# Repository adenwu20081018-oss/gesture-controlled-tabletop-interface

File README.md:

# Gesture-Controlled Tabletop Interface

A camera-based interface for controlling applications with hand gestures. Guess Who is the first application I used to demonstrate it.

[Setup](docs/setup.md) · [Hardware files](hardware/README.md) · [Tests](docs/testing.md)

## Why I Built This

Back in high school, during my Grade 11 year, I spent a lot of time working on this ISP Guess Who game. This game was one of the starting points that sparked my interest in programming and building a game of my own from scratch, from designing the characters and GUI to creating the music. After finishing it, I wasn't satisfied with just letting all that hard work sit in a folder on my computer. I wanted to find a way to bring the game back and do something different with it. With the naive idea of recreating Iron Man's JARVIS system, I decided to try implementing my game in a completely different way, turning it into an interactive tabletop game and controlling it with hand gestures directly on the table.

## How It Works

Camera → Python/OpenCV/MediaPipe → Java Guess Who → Arduino Mega 2560

Python tracks my fingertip and detects a pinch as a selection. Four-point camera calibration maps the interaction area into the game window. Python sends the selection over TCP, and Java uses the same button actions as a mouse click. The Mega's onboard LED responds to character-card actions through USB serial.

I have tested mouse and webcam-pinch control with Arduino LED feedback on my laptop. The resizable interface is ready for a future projector setup, but I have not physically tested tabletop projection or an external webcam yet.

## Hardware

My main prototype uses an ELEGOO Mega 2560, a 400-point half-size breadboard, jumper wires and a PN2222/2N2222A transistor-driven 5V active buzzer. The circuit includes a 470Ω base resistor, 10kΩ pull-down and 1N4007 diode. I have tested the wiring and confirmed that the buzzer works. BUZZ is a standalone command; automatic game sound is not integrated.

[Editable drawing and connections](hardware/breadboard/README.md). My laptop and built-in webcam handle input; a projector is the intended tabletop display. The D13 LED is already on the Mega, so there is no external LED circuit.

## Build Photos

I'll add my own hardware photographs here. Images belong in [photos/](photos/README.md).

<!-- Add real photos here, for example:  -->

## Setup and Files

Start with the [Windows setup guide](docs/setup.md) to install the dependencies, build Java and run hand tracking. Run commands from the repository root so the game can find its assets. See [testing](docs/testing.md) for repeatable checks and [projector setup](docs/projector-setup.md) for calibration and future display use.

| Folder | Contents |
| --- | --- |
| `src/` | Java game and input integration |
| `computer-vision/` | Python hand tracking, pinch detection and calibration |
| `assets/` | Button images, character portraits, interface artwork and audio |
| `arduino/` | Mega firmware, Java serial controller and hardware-free tests |
| `hardware/` | Breadboard drawing and concept PCB design |
| `photos/`, `screenshots/` | Future real build photos and actual game captures |
| `docs/`, `tests/` | Supporting guides and regression tests |

## Challenges Faced

## **Next Step: Concept PCB Design**

I designed this PCB in KiCad to bring the working breadboard buzzer circuit onto a dedicated board. The [editable schematic and routed PCB files](hardware/kicad/buzzer-driver-pcb/) include the components, footprints and copper traces. Fabricating and testing the assembled PCB is the next step.

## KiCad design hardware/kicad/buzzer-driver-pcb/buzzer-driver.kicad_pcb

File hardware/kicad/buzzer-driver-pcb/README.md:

# Interactive Guess Who — Buzzer Driver PCB

**Working Wired Circuit — Editable PCB Design**

A native KiCad 10 daughterboard design for the existing Mega D8 active-buzzer circuit. This is a separate, wired daughterboard, not a shield that plugs directly into the Mega headers. The onboard D13 LED remains on the Mega.

| Native KiCad PCB rendering (not a photograph) | Front copper and footprints |
| --- | --- |
|  |  |

| Top | Bottom |
| --- | --- |
|  |  |

## Design

- 54 × 38 mm chamfered outline; two copper layers; 1.6 mm board thickness assumption.
- Six through-hole components, five electrical nets, 0.45 mm signal tracks and 0.65 mm supply/return tracks.
- Bottom GND copper zone with 0.30 mm clearance and thermal reliefs; explicit ground tracks also connect the ground pads.
- Project minimum clearance 0.25 mm, minimum track width 0.25 mm, copper-to-edge clearance 0.50 mm.
- Green mask appearance, reference designators, connector pin labels, polarity marks and project branding.
- No Gerbers generated; no board manufactured, powered or acoustically tested.

## Arduino interface

| J1 pad | Mega connection | Function |
| --- | --- | --- |
| 1 (square pad) | D8 | R1 input, active-high buzzer control |
| 2 | 5V | Buzzer positive and D1 cathode |
| 3 | GND | Common return |

R1 (470 Ω) drives Q1 base. R2 (10 kΩ) connects base to emitter/GND. Q1 collector switches the buzzer negative terminal. D1 (1N4007) is across the buzzer, cathode/band toward +5V. The existing standalone `BUZZ` firmware command is unchanged; this phase adds no Java sound integration.

## Explicit footprint assumptions

| Part | KiCad footprint / geometry | Qualification |
| --- | --- | --- |
| Q1 | `Package_TO_SOT_THT:TO-92_Inline_Wide`, 2.54 mm adjacent pad pitch | **PCB pad mapping: 1=B, 2=C, 3=E.** Uses generic `Transistor_BJT:Q_NPN_BCE`. The owner has confirmed the transistor wiring works; check that the tested lead arrangement fits these PCB pads before assembly. |
| BZ1 | `Buzzer_Beeper:Buzzer_12x9.5RM7.6`, nominal 12 mm body, 9.5 mm height, 7.6 mm lead pitch | Placeholder for a 5V active buzzer; actual kit buzzer geometry and fit are unverified. Pad 1=positive, pad 2=negative. |
| R1/R2 | `Resistor_THT:R_Axial_DIN0207_L6.3mm_D2.5mm_P10.16mm_Horizontal` | Generic axial resistor body and 10.16 mm formed-lead pitch, not measured kit parts. |
| D1 | `Diode_THT:D_DO-41_SOD81_P10.16mm_Horizontal` | Generic DO-41, 10.16 mm formed-lead pitch; pad 1=cathode. |
| J1 | `Connector_PinHeader_2.54mm:PinHeader_1x03_P2.54mm_Vertical` | Proposed 2.54 mm header, not a keyed connector or Mega mounting pattern. |

All six footprints reference installed KiCad STEP component models. Generic resistor models do not encode the actual resistance color bands. Models illustrate package classes, not exact purchased parts. Successful wired-circuit testing does not by itself establish fit in the selected PCB footprints.

## Open and inspect

1. In KiCad 10, choose **File → Open Existing Project** and select `buzzer-driver.kicad_pro` in this folder.
2. Open `buzzer-driver.kicad_sch` for the editable schematic, or `buzzer-driver.kicad_pcb` for the board.
3. In PCB Editor, use **View → 3D Viewer** (`Alt+3`). Drag to rotate and scroll to zoom.
4. Use **Inspect → Design Rules Checker** to rerun DRC. Enable schematic parity checking. Refill zones with **B** after edits.
5. In Schematic Editor, use **Inspect → Electrical Rules Checker** to rerun ERC.

Install KiCad's standard symbols, footprints and 3D models. Project-local `sym-lib-table` and `fp-lib-table` use KiCad 10 library variables; they do not replace global settings. STEP can be opened in a compatible mechanical CAD viewer, but it does not retain PCB net connectivity.

## Actual checks

KiCad **10.0.8**, 2026-10-31: ERC **0 errors / 0 warnings**; DRC **0 violations**, **0 unconnected pads**, **0 schematic parity problems**. See [validation details](VALIDATION.md) and the unedited reports. The owner subsequently confirmed working PN2222 wiring and buzzer operation. ERC/DRC and the wired-circuit test do not establish PCB package fit, fabrication quality or assembled-board operation.

The three high-resolution PNGs are native `kicad-cli pcb render` ray-traced images, not AI artwork. The layout SVGs are native KiCad copper plots; their PNG previews are rasterizations. The schematic SVG is exported by Eeschema. Morgan Wang's [metronome and buck-converter portfolio](https://portfolio.morgan-wang.workers.dev/) informed the presentation quality; no circuit, layout or image was copied.

## Files

- `buzzer-driver.kicad_pro` — project and design rules.
- `buzzer-driver.kicad_sch` — native schematic using standard symbols.
- `buzzer-driver.kicad_pcb` — native routed board with filled GND zone.
- `buzzer-driver.step` — board and component 3D exchange model.
- `sym-lib-table`, `fp-lib-table` — project-local library references.
- `images/pcb-isometric.png`, `pcb-top.png`, `pcb-bottom.png` — native 3D renders.
- `images/pcb-layout.svg`, `.png` — native front copper/silkscreen plot and preview.
- `images/pcb-bottom-copper.svg` — bottom copper/silkscreen plot and preview.
- `images/buzzer-driver.svg` — native schematic export and preview.
- `reports/erc.rpt`, `drc.rpt`, `netlist.net` — actual KiCad reports and exported netlist.
- `reports/model-check.json` — component model resolution and PCB inventory.
- `VALIDATION.md` — scope, remaining requirements and repeatable CLI commands.
- `generate_project.py` — source generator using KiCad's bundled Python; **overwrites native design files** when run. Do not run it over manual edits. Refill zones and rerun checks/exports after regeneration.
- `README.md` — this guide.

Before any future fabrication: match the tested Q1 wiring to PCB pads, measure BZ1 and all through-hole parts, revise footprints/mappings accordingly, verify selected parts' ratings and the USB power budget, review with the intended fabricator's rules, and repeat ERC/DRC. No purchase or fabrication is needed to view this design.

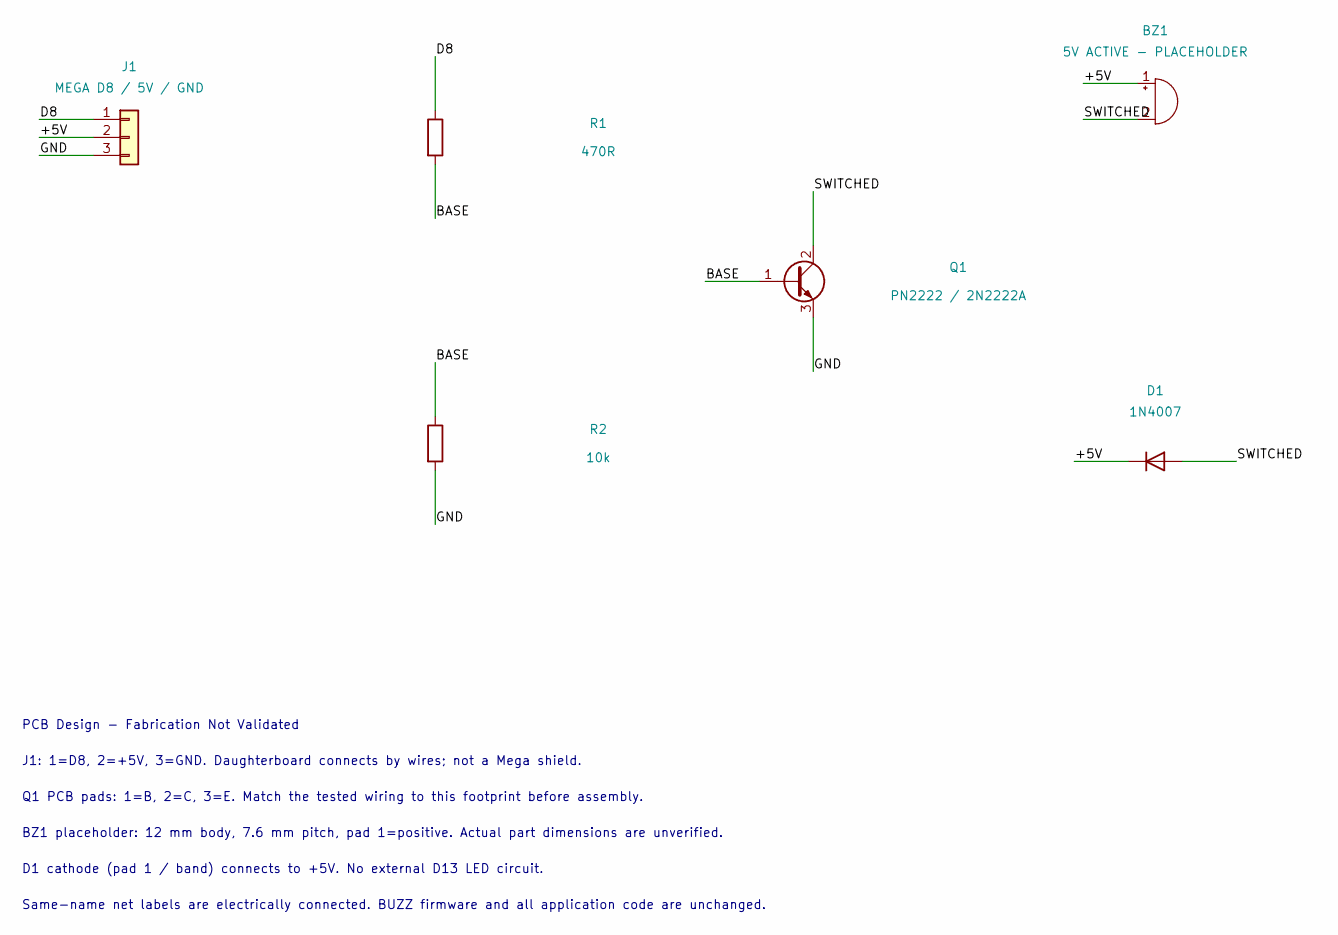
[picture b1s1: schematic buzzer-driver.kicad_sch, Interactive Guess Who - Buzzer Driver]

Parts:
BZ1: 5V ACTIVE - PLACEHOLDER; Buzzer_12x9.5RM7.6
D1: 1N4007; D_DO-41_SOD81_P10.16mm_Horizontal
J1: MEGA D8 / 5V / GND; PinHeader_1x03_P2.54mm_Vertical
Q1: PN2222 / 2N2222A; TO-92_Inline_Wide
R1: 470R; R_Axial_DIN0207_L6.3mm_D2.5mm_P10.16mm_Horizontal
R2: 10k; R_Axial_DIN0207_L6.3mm_D2.5mm_P10.16mm_Horizontal

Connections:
/+5V: BZ1.1 (+), D1.1 (K), J1.2
/BASE: Q1.1 (B), R1.2, R2.1
/D8: J1.1, R1.1
/GND: J1.3, Q1.3 (E), R2.2
/SWITCHED: BZ1.2 (-), D1.2 (A), Q1.2 (C)

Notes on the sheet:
PCB Design - Fabrication Not Validated
J1: 1=D8, 2=+5V, 3=GND. Daughterboard connects by wires; not a Mega shield.
Q1 PCB pads: 1=B, 2=C, 3=E. Match the tested wiring to this footprint before assembly.
BZ1 placeholder: 12 mm body, 7.6 mm pitch, pad 1=positive. Actual part dimensions are unverified.
D1 cathode (pad 1 / band) connects to +5V. No external D13 LED circuit.
Same-name net labels are electrically connected. BUZZ firmware and all application code are unchanged.

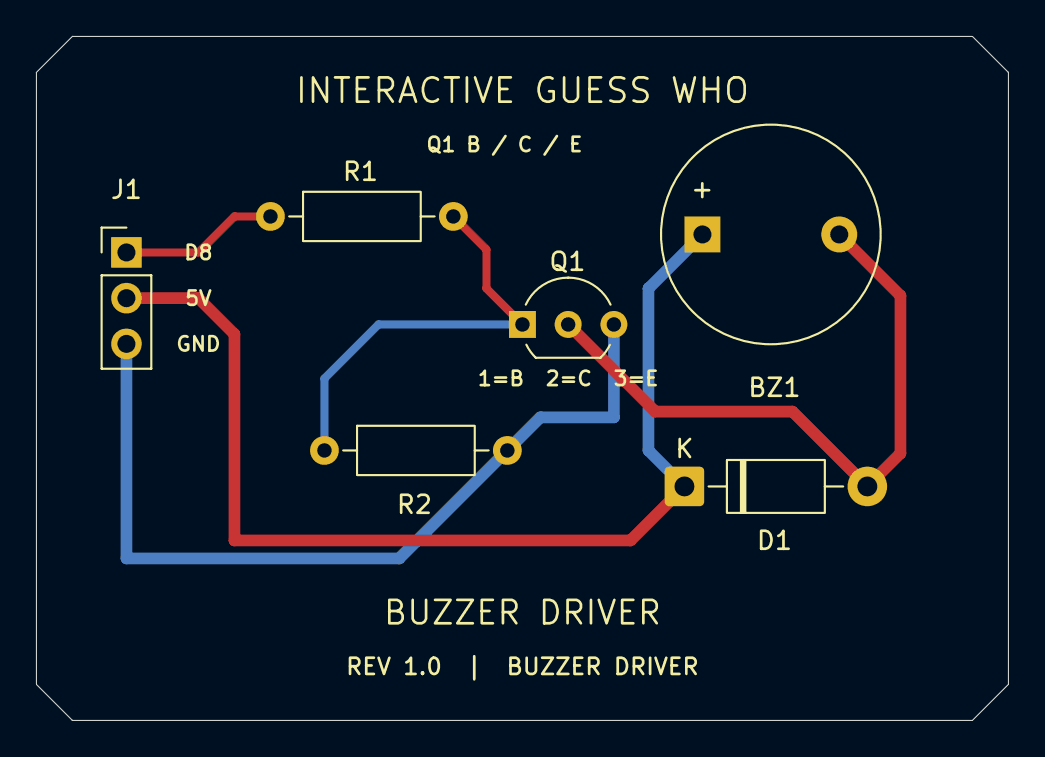
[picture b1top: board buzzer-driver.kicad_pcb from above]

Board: 2 copper layers, 54.0 x 38.0 mm, 6 parts (0 on the bottom side), 5 nets.
